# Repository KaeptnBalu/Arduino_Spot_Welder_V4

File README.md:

# Arduino_Spot_Welder_V4
This is the latest V4 of the Arduino Spot Welder. The previous V3 can be found here https://github.com/KaeptnBalu/Arduino_Spot_Welder_V3

An Arduino based Spot Welder for battery welding

    Build Guide: Car Bundle: https://malectrics.eu/v4-car-battery-bundle-assembly-instructions/ 
                 Lipo Bundle:https://malectrics.eu/v4-lipo-battery-bundle-assembly-instructions/
    Introduction Video: coming soon (Video for previuos V3 https://www.youtube.com/watch?v=CNmvx2JSCvA)
    Project Homepage: https://malectrics.eu/

Improvements in V4:

- Buzzer: With the buzzer alarms will not only be displayed on the screen but also be audible for the user. This makes it much easier to notice an alarm while working with the welder.    
- Temperature Sensor: The temperature sensor will trigger an alarm and disable welding when temperature reaches 65°C to protect the welder from overheating.
- additional 470µF Capacitor: With now two 470µF capacitors it is possible to use weld times up to 100 – 150ms without the risk of the Arduino Nano rebooting. The reboot could happen in V3 at very long weld times because the voltage at the Arduino Nano dropped to low dring the weld.  
- SMD Mosfet Driver: the mosfet driver chip has been changed from the through hole version that was plugged in a socket to a SMD version that is directly soldered to the pcb. The SMD version eliminates eventual contact problems that could happen with the through hole version when it was not plugged in the socket correctly.
- SMD Mosfets: The mosfets have been changed from through hole version to SMD. That will eliminate the problem of failing mosfet legs in V3 on very high currents.
- new aluminum parts: there are still two aluminum parts used on the mosfet board but the parts are just straight and both the same size. This makes producing or modding them for DIY users much easier.    
- Stronger Protection Diodes: The protection diodes on the bottom of the mosfet board have been changed to a much stronger version. They are rated for the same current as the ones in V3 but can take much higher short peak amps and have better heat dissipation because they are phisically bigger.

This Spot Welder can be used to weld 18650 batteries. It uses a 12V car battery as welding current supply. Typically one 60Ah 600A battery delivers enough current to get good welds with 0.15mm - 0.2mm nickel strips. For thicker nickel strips maybe you will need bigger battery or two in paralell. (Maximum 800A total)

The Welder generates a double pulse, where the first one is 12% of the time of the second one by default. Pulse time of the main pulse is adjustable by the rotary encoder and displayed on the screen in ms so you can exactly adjust the time. Its adjustable from 1 … 100 mS by default. (adjustable up to 500ms in the system menu)

If you want to download the project click on "clone or download" on this page. Downloading single files sometimes seems to cause some files to be corrupted while downloading.

You can get parts to build your own Spot Welder or prebuilt kits at https://malectrics.eu/

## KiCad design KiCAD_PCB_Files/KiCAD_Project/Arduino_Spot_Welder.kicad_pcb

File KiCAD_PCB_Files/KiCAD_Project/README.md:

These are the KICAD project files for the Arduino Spot Welder V4

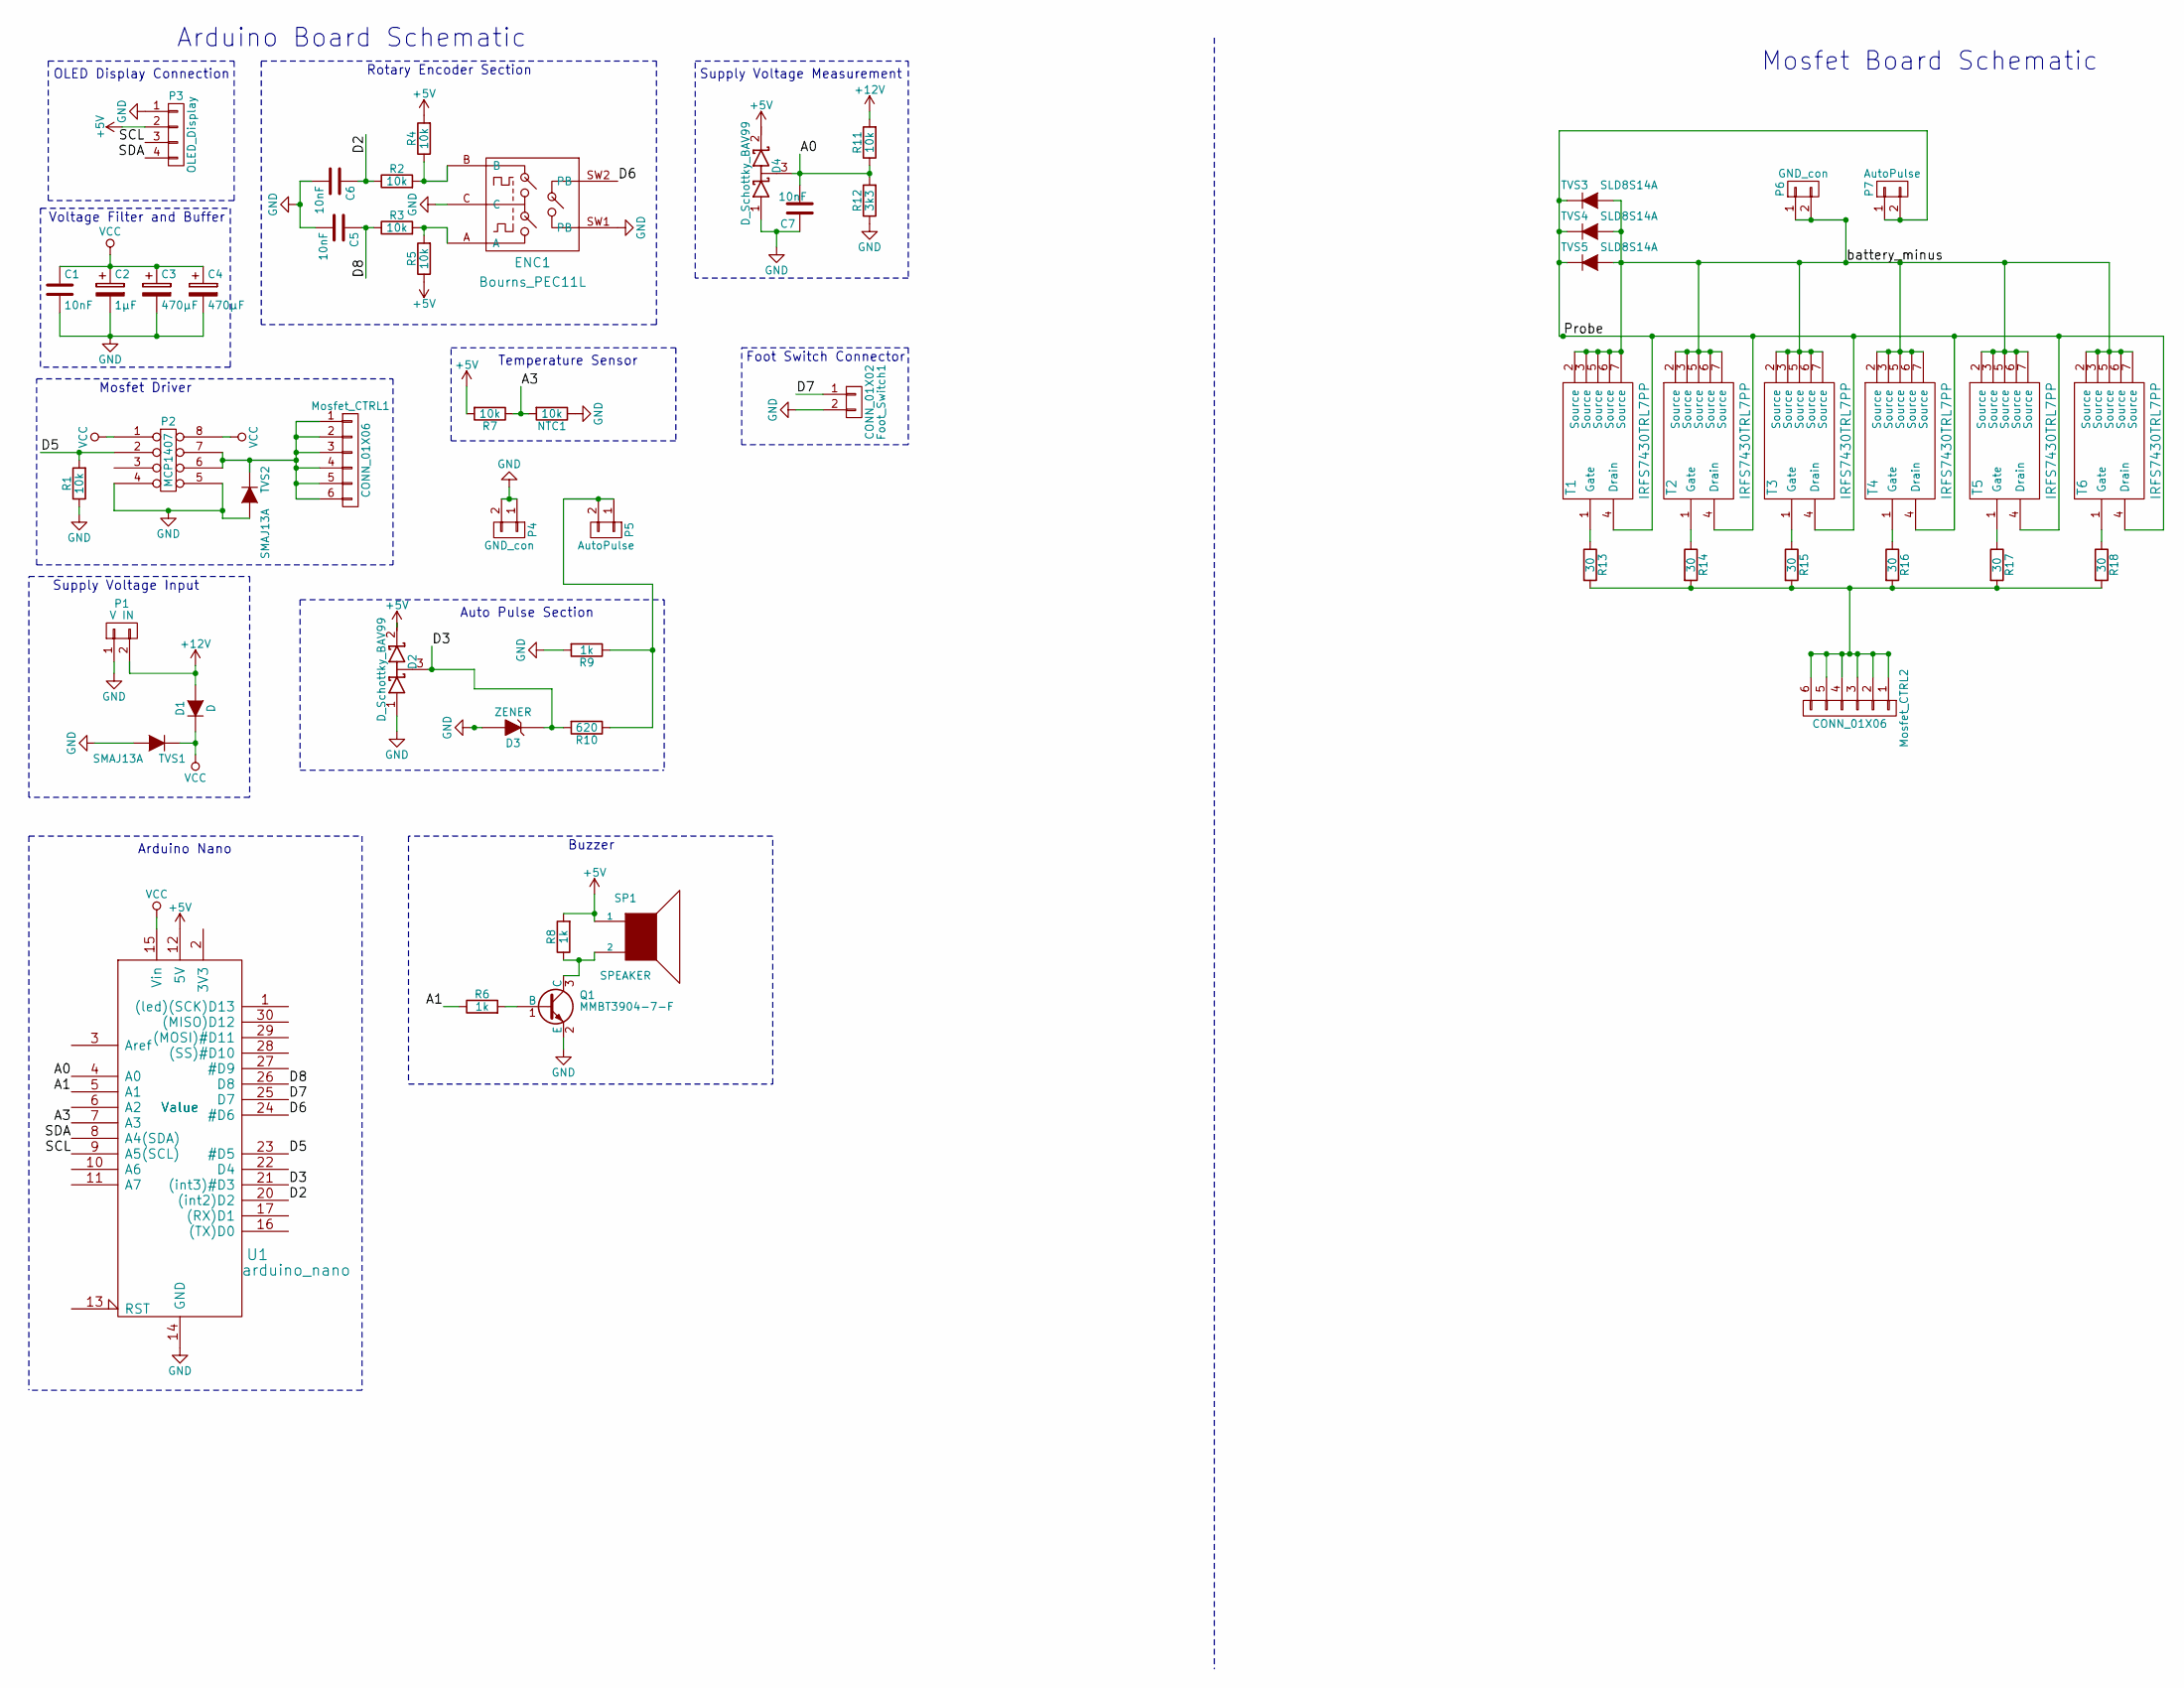
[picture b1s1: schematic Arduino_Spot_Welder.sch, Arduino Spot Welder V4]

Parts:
C1, C5: 10nF; C_0805_HandSoldering
C2: 1µF; C_Disc_D7.5mm_W5.0mm_P5.00mm
C3: 470µF; CP_Elec_10x10
C4: 470µF; CP_Elec_10x10; MFG Part Number Value
C6, C7: 10nF; C_0805_HandSoldering; MFG Part Number Value
D1: D; D_SMA
D2, D4: D_Schottky_BAV99; SOT-23; MFG Part Number BAV99Q-7-F
D3: ZENER; D_SOD-123
ENC1: Bourns_PEC11L; ALPS_STEC12E08; MFG Part Number PEC11L-4220F-S0015
Foot_Switch1: CONN_01X02; Molex_KK-6410-02_02x2.54mm_Straight
Mosfet_CTRL1, Mosfet_CTRL2: CONN_01X06; Pin_Header_Straight_1x06_Pitch2.54mm
NTC1: 10k; R_0805_HandSoldering; MFG Part Number NCP21XV103J03RA
P1: V IN; Terminal_Block_2P_3.5mm; MFG Part Number Value
P2: MCP1407; SOIC-8_3.9x4.9mm_Pitch1.27mm; MFG Part Number MCP1407-E/SN
P3: OLED_Display; OLED_SSD1306_128x64
P4, P6: GND_con; Pin_Header_Straight_1x02_Pitch2.54mm
P5, P7: AutoPulse; Pin_Header_Straight_1x02_Pitch2.54mm
Q1: MMBT3904-7-F; SOT-23; MFG Part Number MMBT3904-7-F
R1, R2, R3, R4, R5, R11: 10k; R_0805_HandSoldering
R6, R8, R9: 1k; R_0805_HandSoldering; MFG Part Number Value
R7: 10k; R_0805_HandSoldering; MFG Part Number Value
R10: 620; R_0805_HandSoldering
R12: 3k3; R_0805_HandSoldering; MFG Part Number Value
R13, R14, R15, R16, R17, R18: 30; R_1206_HandSoldering
SP1: SPEAKER; Buzzer_PS1240P02BT; MFG Part Number PS1240P02BT
T1, T2, T3, T4, T5, T6: IRFS7430TRL7PP; TO-263-6
TVS1, TVS2: SMAJ13A; D_SMA; MFG Part Number SMAJ13A-13-F
TVS3, TVS4, TVS5: SLD8S14A; SMTO-263; MFG Part Number SLD8S14A
U1: arduino_nano; arduino_mini; MFG Part Number Value

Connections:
+5V: D2.2 (K), D4.2 (K), P3.2, R4.2, R5.1, R7.2, R8.2, SP1.1, U1.12 (5V)
+12V: D1.2 (A), P1.2, R11.2
/A0: C7.2, D4.3 (common), R11.1, R12.2, U1.4 (A0)
/A1: R6.1, U1.5 (A1)
/A3: NTC1.2, R7.1, U1.7 (A3)
/D2: C6.1, R2.1, U1.20 ((int2)D2)
/D3: D2.3 (common), D3.1 (K), R10.2, U1.21 ((int3)#D3)
/D5: P2.2, R1.2, U1.23 (#D5)
/D6: ENC1.SW2 (PB), U1.24 (#D6)
/D7: Foot_Switch1.1, U1.25 (D7)
/D8: C5.1, R3.1, U1.26 (D8)
/Probe: P7.1, P7.2, T1.4 (Drain), T2.4 (Drain), T3.4 (Drain), T4.4 (Drain), T5.4 (Drain), T6.4 (Drain), TVS3.1 (K), TVS4.1 (K), TVS5.1 (K)
/SCL: P3.3, U1.9 (A5(SCL))
/SDA: P3.4, U1.8 (A4(SDA))
/battery_minus: P6.1, P6.2, T1.2 (Source), T1.3 (Source), T1.5 (Source), T1.6 (Source), T1.7 (Source), T2.2 (Source), T2.3 (Source), T2.5 (Source), T2.6 (Source), T2.7 (Source), T3.2 (Source), T3.3 (Source), T3.5 (Source), T3.6 (Source), T3.7 (Source), T4.2 (Source), T4.3 (Source), T4.5 (Source), T4.6 (Source), T4.7 (Source), T5.2 (Source), T5.3 (Source), T5.5 (Source), T5.6 (Source), T5.7 (Source), T6.2 (Source), T6.3 (Source), T6.5 (Source), T6.6 (Source), T6.7 (Source), TVS3.2 (A), TVS4.2 (A), TVS5.2 (A)
GND: C1.2, C2.2, C3.2, C4.2, C5.2, C6.2, C7.1, D2.1 (A), D3.2 (A), D4.1 (A), ENC1.C, ENC1.SW1 (PB), Foot_Switch1.2, NTC1.1, P1.1, P2.4, P2.5, P3.1, P4.1, P4.2, Q1.2 (E), R1.1, R9.2, R12.1, TVS1.2 (A), TVS2.2 (A), U1.14 (GND), U1.19 (GND)
unnamed: ENC1.A, R3.2, R5.2
unnamed: ENC1.B, R2.2, R4.1
unnamed: Mosfet_CTRL1.1, Mosfet_CTRL1.2, Mosfet_CTRL1.3, Mosfet_CTRL1.4, Mosfet_CTRL1.5, Mosfet_CTRL1.6, P2.6, P2.7, TVS2.1 (K)
unnamed: Mosfet_CTRL2.1, Mosfet_CTRL2.2, Mosfet_CTRL2.3, Mosfet_CTRL2.4, Mosfet_CTRL2.5, Mosfet_CTRL2.6, R13.2, R14.2, R15.2, R16.2, R17.2, R18.2
unnamed: P5.1, P5.2, R9.1, R10.1
unnamed: Q1.1 (B), R6.2
unnamed: Q1.3 (C), R8.1, SP1.2
unnamed: R13.1, T1.1 (Gate)
unnamed: R14.1, T2.1 (Gate)
unnamed: R15.1, T3.1 (Gate)
unnamed: R16.1, T4.1 (Gate)
unnamed: R17.1, T5.1 (Gate)
unnamed: R18.1, T6.1 (Gate)
VCC: C1.1, C2.1, C3.1, C4.1, D1.1 (K), P2.1, P2.8, TVS1.1 (K), U1.15 (Vin)

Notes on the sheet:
Arduino Board Schematic
Mosfet Board Schematic
Auto Pulse Section
OLED Display Connection
Rotary Encoder Section
Supply Voltage Measurement
Supply Voltage Input
Buzzer
Mosfet Driver
Voltage Filter and Buffer
Foot Switch Connector
Arduino Nano
Temperature Sensor

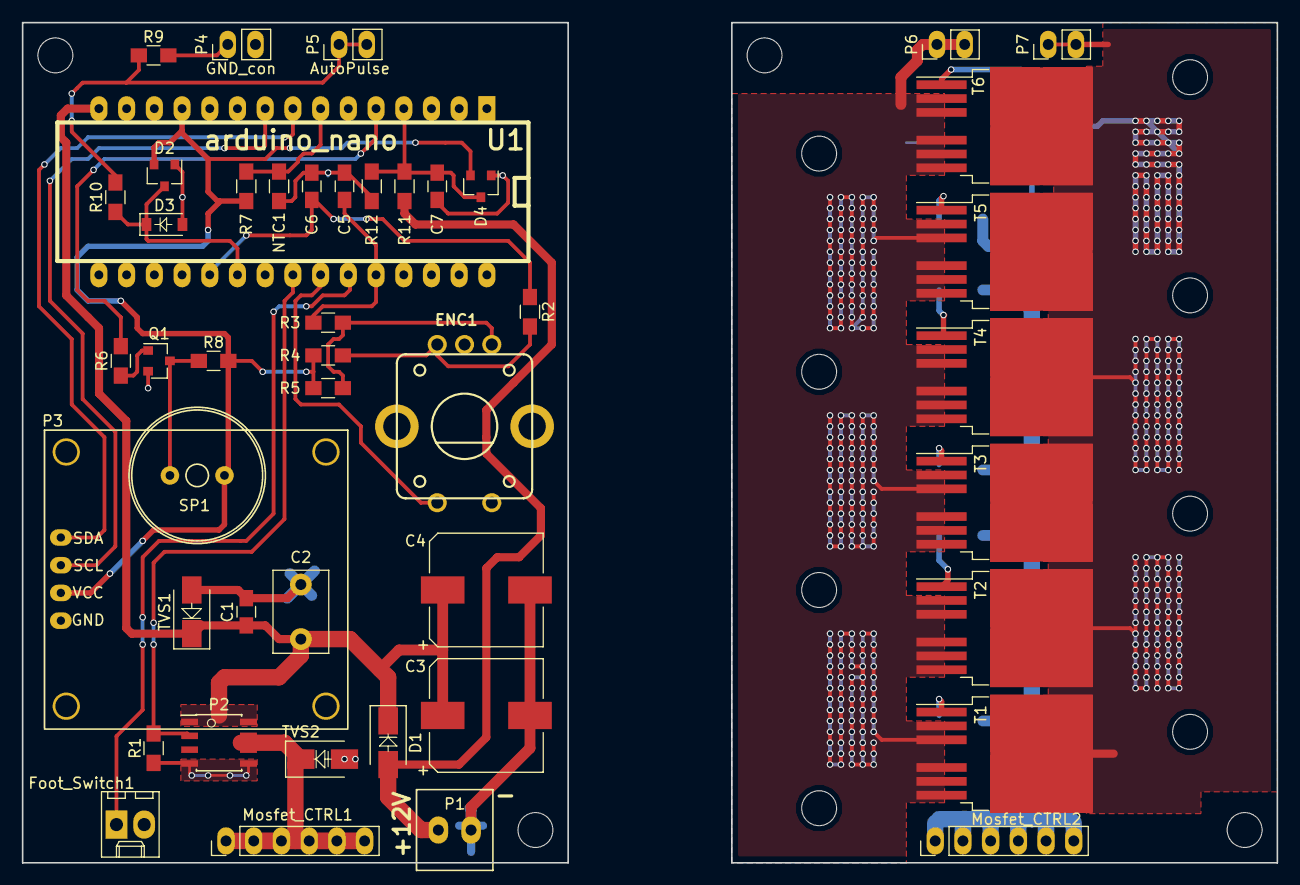
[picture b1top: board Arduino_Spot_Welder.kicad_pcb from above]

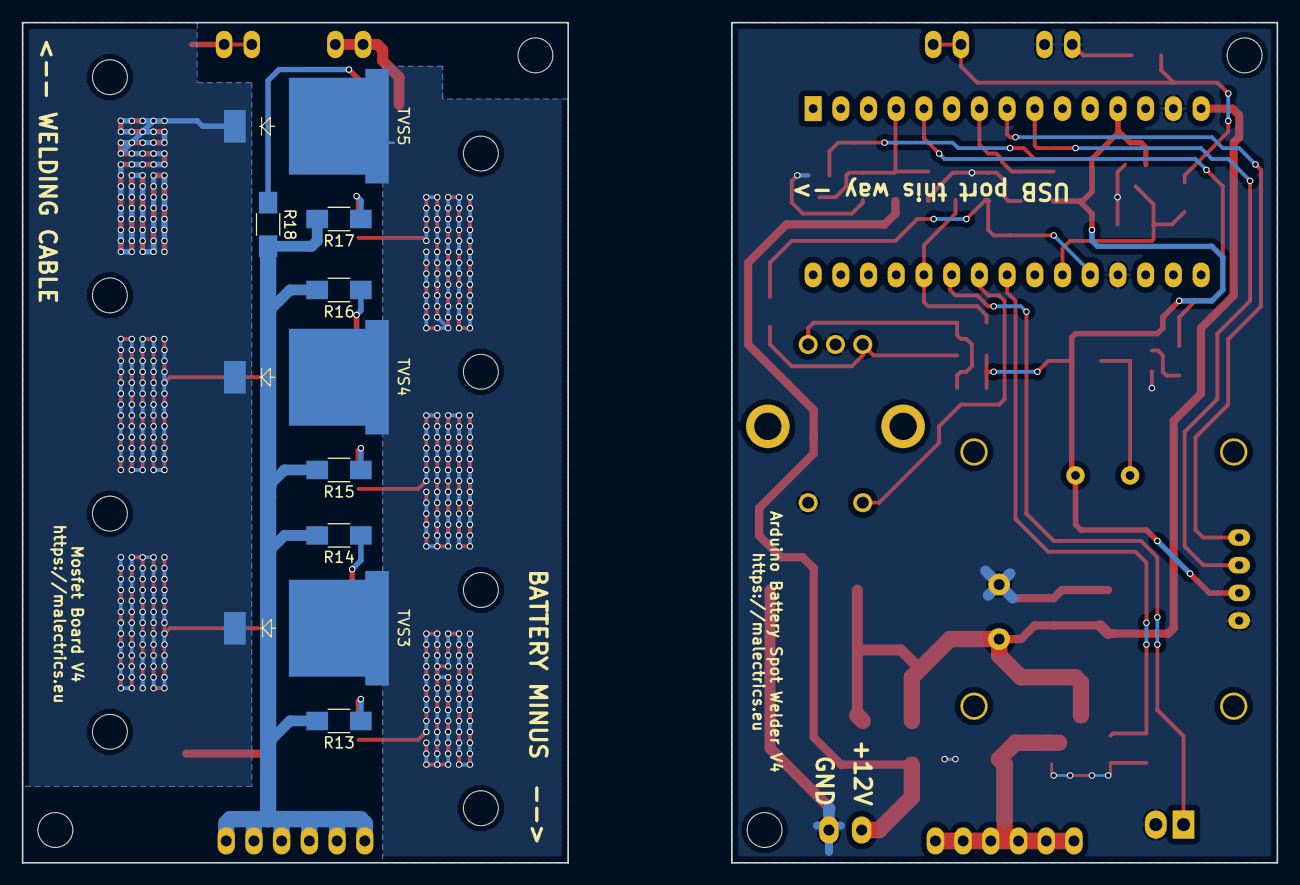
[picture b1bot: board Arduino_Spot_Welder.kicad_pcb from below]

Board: 2 copper layers, 115.0 x 77.0 mm, 55 parts (9 on the bottom side), 30 nets.

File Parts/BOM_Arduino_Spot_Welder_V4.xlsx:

|  | BOM Arduino Spot Welder V4
 |  |  |  | Mouser.com Parts
 |  | Quantity | PCB Reference | Name | Mouser.com Part Number | Note
 |  | 8 | IRFS7430TRL7PP | Mosfet IRFS7430TRL7PP 40V 522A | 942-IRFS7430TRL7PP
 |  | 1 | MCP1407 | Mosfet Driver MCP1407-E/SN | 579-MCP1407-E/SN
 |  | 1 | Bourns_PEC11L | Rotary Encoder | 652-PEC11L4220FS0015
 |  | 2 | U1 Arduino Nano | 1x15 Pol Female Pin Header | 992-15FX1-254MM
 |  | 1 | Mosfet_CTRL2 | 1x8pol female header | 437-8018700810001101
 |  | 2 | P6,P7 | 1x2pol female header | 437-8018700210001101
 |  | 1 | OLED_Display | 1x4pol female header | 517-974-01-04-RK
 |  | 1 | Mosfet_CTRL1, P4, P5 | 1x16 Pol Male Pin Header | 538-22-28-4160
 |  | 1 | Foot_Switch1 | PCB connector 2pin | 710-61900211121
 |  | 1 | P1 | Terminal Block | 710-691214110002
 |  | 1 | P2 MCP1407 | IC socket 8 pole | 571-1-2199298-2
 |  | 1 | D1 | SMD-Schottky 60V 1A | 750-CDBA160-G
 |  | 1 | Zener D3 | SMD Zener diode 4,3V 0,5W | 78-MMSZ4687-E3-08
 |  | 2 | D2,D4 | Schottky BAV99 | 78-BAV99-E3-08
 |  | 4 | TVS3,TVS4,TVS5 | TVS Diode 15,6V 7kW | 576-SLD8S14A
 |  | 1 | TVS1,TVS2 | TVS Diode 14,4V 400W | 621-SMAJ13A-13-F
 |  | 1 | C2 | film capacitor 1 µF RM5 | 505-MKS2C041001FMSSD
 |  | 4 | C1, C5, C6, C7 | ceramic capacitor 0,01µF SMD | 80-C0805C103J5R
 |  | 1 | C3,C4 | electrolytic capacitor 470µF 25V | 647-UWT1E471MNL1S
 |  | 1 | Q1 | Bipolartransistor 200mA | 621-MMBT3904-F
 |  | 1 | SP1 | Piezzo Speaker | 810-PS1240P02BT
 |  | 1 | NTC1 | NTC Thermistor | 81-NCP21XV103J03RA
 |  | 1 | R1;R2,R3,R4,R5,R7,R11 | Resistor 0805 SMD 10 kOhm | 603-RC0805FR-0710KL
 |  | 10 | R6,R8,R9 | Resistor 0805 SMD 1 kOhm | 603-RC0805FR-071KL
 |  | 10 | R10 | Resistor 0805 SMD 620 Ohm | 603-RC0805FR-07620RL
 |  | 10 | R12 | Resistor 0805 SMD 3,3 kOhm | 603-RC0805FR-133K3L
 |  | 10 | R13 … R18 | Resistor 1206 SMD 30 Ohm | 603-RC1206FR-0730RL
 |  |  |  |  | Other Parts
 |  | Quantity |  | Name | Description | Link / Where to buy
 |  | 1 |  | Arduino Nano |  | https://www.banggood.com/de/Geekcreit-ATmega328P-Nano-V3-Con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
 |  | 1 |  | OLED Diplay 0,96" 128x64 | take care of correct pinout (GND - VCC - SCL - SDA) | https://www.banggood.com/Geekcreit-0_96-Inch-OLED-I2C-IIC-Co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
 |  | 1 |  | Alu 90*15*4mm | see alu_template.pdf | local hardware Store or https://malectrics.eu/
 |  | 8 |  | M3x8 screw + nuts | for Alu Parts assembly | local hardware store
 |  | 2 |  | M3x20 screw | to screw pcbs together | local hardware store
 |  | 6 |  | M3 Nylon Nuts | to screw pcbs together | Ebay or Aliexpress
 |  | 1 |  | 1m 10 mm² - 16mm² flexible silicone cable | for 2pcs 0,5m welding cables | Ebay or Aliexpress
 |  | 1 |  | 0,1m 10mm² - 16mm² solid copper wire | for the welding tips | local hardware store or welding tips from https://malectrics.eu/
 |  | 2 |  | cable shoe for 10 mm² or 16mm2 | for welding cable | local hardware store or https://malectrics.eu/
 |  | 2 |  | cable connector for 10 mm² or 16mm2 | welding tip connection to the welding cables | local hardware store or https://malectrics.eu/
 |  | 1 |  | battery terminals | for car battery | local hardware store or https://malectrics.eu/
 |  | 1 |  | PCB Set | Arduino + Mosfet PCB | https://malectrics.eu/
 |  | 2 |  | nylon spacers M2 x 12mm + M2x5 screws for OLED display | OPTIONAL | Ebay or Aliexpress
 |  | 1 |  | Foot Switch | OPTIONAL | https://malectrics.eu/
 |  | 1 |  | 3d printed case | OPTIONAL | https://github.com/KaeptnBalu/Arduino_Spot_Welder_V4/tree/ma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
 |  | 1 |  | 300A Fuse | OPTIONAL | https://malectrics.eu/

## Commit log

2021-03-17 replace defective file
2021-08-18 Create Readme.md
    These are the gerber files for the Arduino PCB V4. This one can be ordered with the standard 1oz copper layer.
2021-08-18 Create Readme.md
    These are the Gerber files for the Mosfet PCB V4. Please order it with 4oz copper layer at the pcb manufacturer because it needs to take a lot of current.
2026-05-12 Update purchase links for Arduino and OLED display
